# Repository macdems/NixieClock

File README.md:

# IN-14 Nixie Clock

A connected **IN-14 Nixie tube clock** combining classic display technology with modern embedded control.  
This repository contains the complete project: **firmware**, **electrical schematic**, **PCB design**, and **case design**.

## Overview

The project is built around an ESP-based controller and drives IN-14 Nixie tubes to display time with network-connected features such as:

- **Automatic time synchronization**
- **MQTT integration**
- **OTA firmware updates**
- **Persistent settings storage**

## Repository Contents

- **Firmware** — ESP-IDF project for clock control, MQTT, OTA, and LEDs
- **Schematic** — electrical design of the clock hardware
- **PCB** — board layout and manufacturing files
- **Case design** — enclosure files for the finished device

## Firmware Features

- IN-14 time display control
- Wi-Fi connectivity
- SNTP time synchronization
- MQTT status and command topics
- Home Assistant discovery support
- OTA firmware update over HTTPS
- LED effects and persisted LED state

## Hardware

This project is designed for **IN-14 Nixie tubes** and includes the supporting electronics required for:

- high-voltage tube driving
- logic/control circuitry
- power distribution
- decorative or ambient LED lighting

### Bill of Materials (BOM)

| Ref                                | Qty | Value               | Description                                                                       |
| ---------------------------------- | --- | ------------------- | --------------------------------------------------------------------------------- |
| C1                                 | 1   | 220µF/35V           | electrolytic capacitor THT radial D5.0mm P2.50mm                                  |
| C2                                 | 1   | 220µF               | electrolytic capacitor THT radial D5.0mm P2.50mm                                  |
| D1, D2, D3, D4                     | 4   | WS2812B             | WS2812B-1209 SMD mount LED                                                        |
| D5, D7                             | 2   | SS24                | SMA package                                                                       |
| D6                                 | 1   | ES1G                | SMA package                                                                       |
| HS1                                | 1   | T8WC                | heatsink for for TO-220 (<https://aliexpress.com/item/1005006082544471.html>)     |
| J1                                 | 1   | 12V                 | 01x02 screw terminal P5.08mm                                                      |
| J2                                 | 1   | 180V                | 01x02 screw terminal P5.08mm                                                      |
| L1                                 | 1   | 150mH               | SMD inductor L_10.4x10.4 H4.8                                                     |
| N1, N2, N3, N4                     | 4   | IN-14               | Nixie IN-14                                                                       |
| N5                                 | 1   |                     | 02×02 pin socket P2.54mm                                                          |
| N5                                 | 1   |                     | Nixie colon separator (<https://aliexpress.com/item/1005009385409998.html>)       |
| Q1, Q2, Q3, Q4, Q5, Q6, Q7, Q8, Q9 | 9   | MMBTA44             | SOT-23 package                                                                    |
| R1, R2, R3, R4                     | 4   | 12k                 | 1026 SMD                                                                          |
| R5, R6                             | 2   | 390k                | 1026 SMD                                                                          |
| U1, U2, U3, U4                     | 4   | SN74141N            | DIP-16 W7.62mm                                                                    |
| U5, U6, U7                         | 3   | 74HC595             | DIP-16 W7.62mm                                                                    |
| U8                                 | 1   | LM2596T-5           | TO-220-5                                                                          |
| U9                                 | 1   | ESP32-C3 Super Mini |                                                                                   |
|                                    | 1   | NCH6100HV           | high voltage DC power supply for Nixie tubes                                      |
|                                    | 6   | M3×5×4              | brass insert M3 H5mm OD4mm                                                        |
|                                    | 2   | M2.5×3×3.5          | brass insert M2.5 H3mm OD3.5mm                                                    |
|                                    | 1   | DC022B              | DC power jack supply socket (<https://aliexpress.com/item/1005005583190148.html>) |

### Manufacturing

1. Order the PCB from a manufacturer such as **JLCPCB** or **PCBWay**using the provided KICAD project files.
2. Assemble the components according to the schematic and PCB layout.
3. 3D print or fabricate the case using the provided FreeCAD design files.
4. Paint the case if desired and allow to dry before final assembly.
5. Mount the DC power jack and brass inserts into the case, then secure the PCB inside the case using screws and inserts.
6. Solder wires to the DC power jack and connect them to both 12V input of the PCB and the NCH6100HV power supply input. Ensure proper polarity and secure connections. 
7. Connect the NCH6100HV 180V output to the J2 high voltage input on the PCB, ensuring secure and insulated connections to prevent accidental contact with high voltage.

## Build

Firmware is based on **ESP-IDF**. First you need to configure it, specyfying your WiFi and MQTT creedentials. Then you can build and flash the firmware with:

```bash
idf.py build
idf.py -p <PORT> flash monitor
```

Configuration can be adjusted with:

```bash
idf.py menuconfig
```

## Project Structure

```text
main/               ESP-IDF application sources
PCB/                PCB layout and fabrication files
NixieClock.FCStd    FreeCAD case design file
NixieClock.3mf      Case design export for 3D printing
```

## Notes

Nixie clocks operate with **high voltage**. Hardware assembly, probing, and testing should be performed carefully and only with appropriate experience.

## License

This project is licensed under the **Creative Commons Attribution-ShareAlike 4.0 International (CC BY-SA 4.0)** license.  
See the [`LICENSE.md`](LICENSE.md) file for full license text.

## Status

This repository is intended as a complete source package for building an IN-14 Nixie clock from electronics to enclosure.

---
A compact Nixie clock project with both vintage character and modern connectivity.

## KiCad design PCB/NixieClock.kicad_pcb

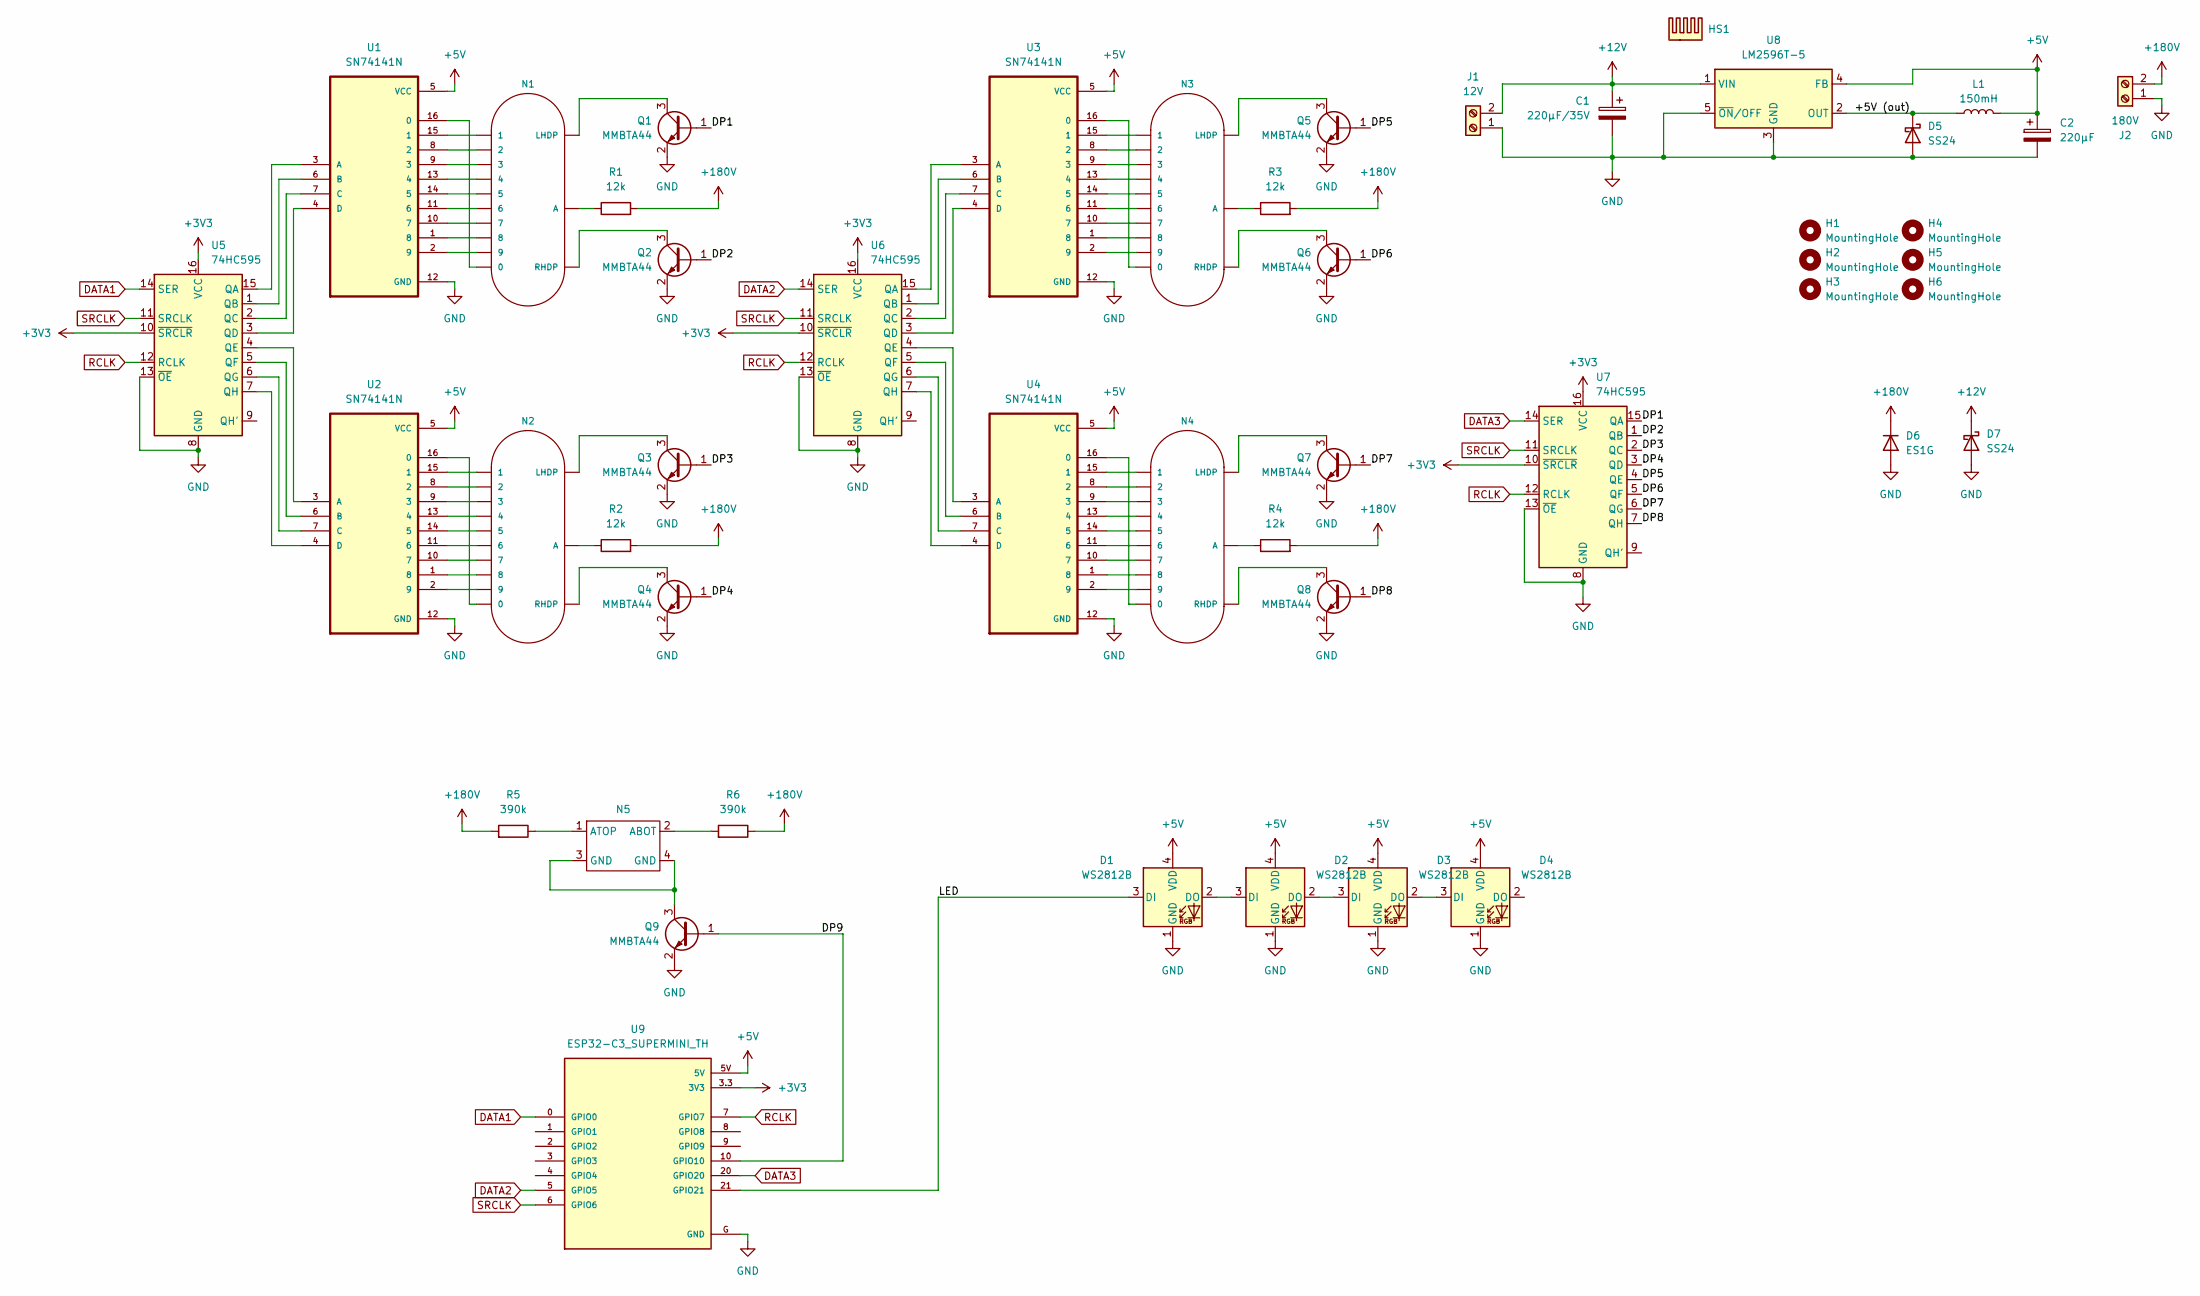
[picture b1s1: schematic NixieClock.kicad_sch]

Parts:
C1: 220µF/35V; CP_Radial_D5.0mm_P2.50mm
C2: 220µF; CP_Radial_D5.0mm_P2.50mm
D1, D2, D3, D4: WS2812B; LED-SMD_4P-L3.2-W2.7-TL-WS2812B-1209
D5, D7: SS24; D_SMA_Handsoldering
D6: ES1G; D_SMA_Handsoldering
H1, H2, H3, H4, H5, H6: MountingHole; MountingHole_3.2mm_M3
HS1: Heatsink; Heatsink_T8WC_TO-220
J1: 12V; TerminalBlock_bornier-2_P5.08mm
J2: 180V; TerminalBlock_bornier-2_P5.08mm
L1: 150mH; L_10.4x10.4_H4.8
N1, N2, N3, N4: IN-14
N5: PinSocket_2x02_P2.54mm_Vertical
Q1, Q2, Q3, Q4, Q5, Q6, Q7, Q8, Q9: MMBTA44; SOT-23_Handsoldering
R1, R2, R3, R4: 12k; R_1206_3216Metric_Pad1.30x1.75mm_HandSolder
R5, R6: 390k; R_1206_3216Metric_Pad1.30x1.75mm_HandSolder
U1, U2, U3, U4: SN74141N; DIP-16_W7.62mm
U5, U6, U7: 74HC595; DIP-16_W7.62mm
U8: LM2596T-5; TO-220-5_P3.4x3.7mm_StaggerOdd_Lead3.8mm_Vertical
U9: ESP32-C3_SUPERMINI_TH; MODULE_ESP32-C3_SUPERMINI_TH

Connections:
+3V3: U5.10 (~SRCLR), U5.16 (VCC), U6.10 (~SRCLR), U6.16 (VCC), U7.10 (~SRCLR), U7.16 (VCC), U9.3.3 (3V3)
+5V: C2.1, D1.4 (VDD), D2.4 (VDD), D3.4 (VDD), D4.4 (VDD), L1.2, U1.5 (VCC), U2.5 (VCC), U3.5 (VCC), U4.5 (VCC), U8.4 (FB), U9.5V
+12V: C1.1, D7.1 (K), J1.2, U8.1 (VIN)
+180V: D6.1 (K), J2.2, R1.2, R2.2, R3.2, R4.2, R5.2, R6.1
/+5V (out): D5.1 (K), L1.1, U8.2 (OUT)
/DP1: Q1.1 (B), U7.15 (QA)
/DP2: Q2.1 (B), U7.1 (QB)
/DP3: Q3.1 (B), U7.2 (QC)
/DP4: Q4.1 (B), U7.3 (QD)
/DP5: Q5.1 (B), U7.4 (QE)
/DP6: Q6.1 (B), U7.5 (QF)
/DP7: Q7.1 (B), U7.6 (QG)
/DP8: Q8.1 (B), U7.7 (QH)
/DP9: Q9.1 (B), U9.10 (GPIO10)
/LED: D1.3 (DI), U9.21 (GPIO21)
DATA1: U5.14 (SER), U9.0 (GPIO0)
DATA2: U6.14 (SER), U9.5 (GPIO5)
DATA3: U7.14 (SER), U9.20 (GPIO20)
GND: C1.2, C2.2, D1.1 (GND), D2.1 (GND), D3.1 (GND), D4.1 (GND), D5.2 (A), D6.2 (A), D7.2 (A), J1.1, J2.1, Q1.2 (E), Q2.2 (E), Q3.2 (E), Q4.2 (E), Q5.2 (E), Q6.2 (E), Q7.2 (E), Q8.2 (E), Q9.2 (E), U1.12 (GND), U2.12 (GND), U3.12 (GND), U4.12 (GND), U5.8 (GND), U5.13 (~OE), U6.8 (GND), U6.13 (~OE), U7.8 (GND), U7.13 (~OE), U8.3 (GND), U8.5 (~ON/OFF), U9.G (GND)
unnamed: D1.2 (DO), D2.3 (DI)
unnamed: D2.2 (DO), D3.3 (DI)
unnamed: D3.2 (DO), D4.3 (DI)
unnamed: N1.A, R1.1
unnamed: N2.A, R2.1
unnamed: N3.A, R3.1
unnamed: N4.A, R4.1
unnamed: N5.2 (ABOT), R6.2
unnamed: N5.1 (ATOP), R5.1
unnamed: N1.LHDP, Q1.3 (C)
unnamed: N1.RHDP, Q2.3 (C)
unnamed: N2.LHDP, Q3.3 (C)
unnamed: N2.RHDP, Q4.3 (C)
unnamed: N3.LHDP, Q5.3 (C)
unnamed: N3.RHDP, Q6.3 (C)
unnamed: N4.LHDP, Q7.3 (C)
unnamed: N4.RHDP, Q8.3 (C)
unnamed: N5.3 (GND), N5.4 (GND), Q9.3 (C)
unnamed: N1.0, U1.16 (0)
unnamed: N1.1, U1.15 (1)
unnamed: N1.2, U1.8 (2)
unnamed: N1.3, U1.9 (3)
unnamed: N1.4, U1.13 (4)
unnamed: N1.5, U1.14 (5)
unnamed: N1.6, U1.11 (6)
unnamed: N1.7, U1.10 (7)
unnamed: N1.8, U1.1 (8)
unnamed: N1.9, U1.2 (9)
unnamed: U1.3 (A), U5.15 (QA)
unnamed: U1.6 (B), U5.1 (QB)
unnamed: U1.7 (C), U5.2 (QC)
unnamed: U1.4 (D), U5.3 (QD)
unnamed: N2.0, U2.16 (0)
unnamed: N2.1, U2.15 (1)
unnamed: N2.2, U2.8 (2)
unnamed: N2.3, U2.9 (3)
unnamed: N2.4, U2.13 (4)
unnamed: N2.5, U2.14 (5)
unnamed: N2.6, U2.11 (6)
unnamed: N2.7, U2.10 (7)
unnamed: N2.8, U2.1 (8)
unnamed: N2.9, U2.2 (9)
unnamed: U2.3 (A), U5.4 (QE)
unnamed: U2.6 (B), U5.5 (QF)
unnamed: U2.7 (C), U5.6 (QG)
unnamed: U2.4 (D), U5.7 (QH)
unnamed: N3.0, U3.16 (0)
unnamed: N3.1, U3.15 (1)
unnamed: N3.2, U3.8 (2)
unnamed: N3.3, U3.9 (3)
unnamed: N3.4, U3.13 (4)
unnamed: N3.5, U3.14 (5)
unnamed: N3.6, U3.11 (6)
unnamed: N3.7, U3.10 (7)
unnamed: N3.8, U3.1 (8)
unnamed: N3.9, U3.2 (9)
unnamed: U3.3 (A), U6.15 (QA)
unnamed: U3.6 (B), U6.1 (QB)
unnamed: U3.7 (C), U6.2 (QC)
unnamed: U3.4 (D), U6.3 (QD)
unnamed: N4.0, U4.16 (0)
unnamed: N4.1, U4.15 (1)
unnamed: N4.2, U4.8 (2)
unnamed: N4.3, U4.9 (3)
unnamed: N4.4, U4.13 (4)
unnamed: N4.5, U4.14 (5)
unnamed: N4.6, U4.11 (6)
unnamed: N4.7, U4.10 (7)
unnamed: N4.8, U4.1 (8)
unnamed: N4.9, U4.2 (9)
unnamed: U4.3 (A), U6.4 (QE)
unnamed: U4.6 (B), U6.5 (QF)
unnamed: U4.7 (C), U6.6 (QG)
unnamed: U4.4 (D), U6.7 (QH)
RCLK: U5.12 (RCLK), U6.12 (RCLK), U7.12 (RCLK), U9.7 (GPIO7)
SRCLK: U5.11 (SRCLK), U6.11 (SRCLK), U7.11 (SRCLK), U9.6 (GPIO6)

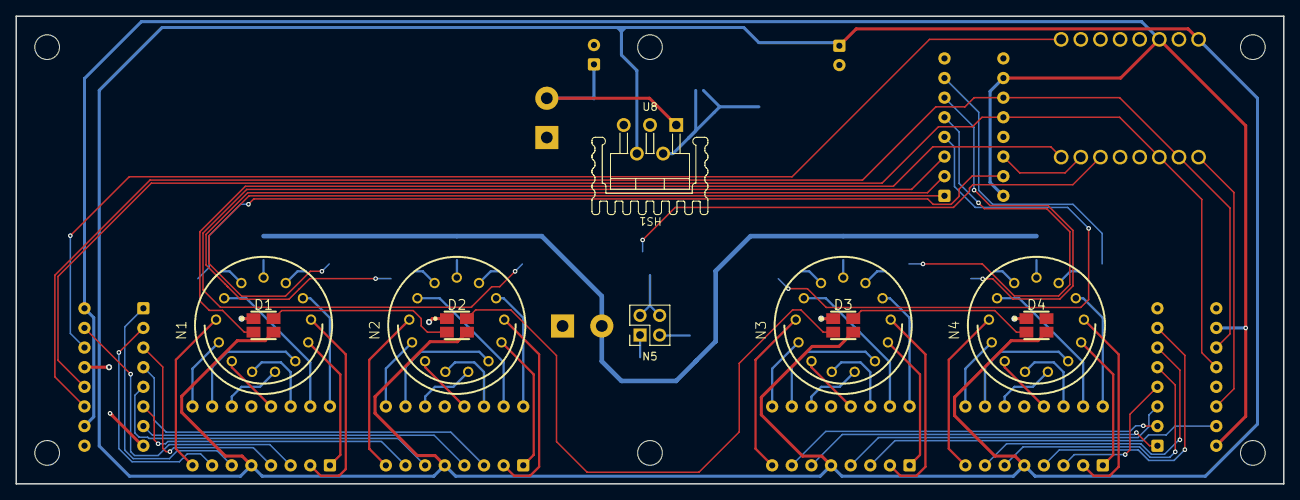
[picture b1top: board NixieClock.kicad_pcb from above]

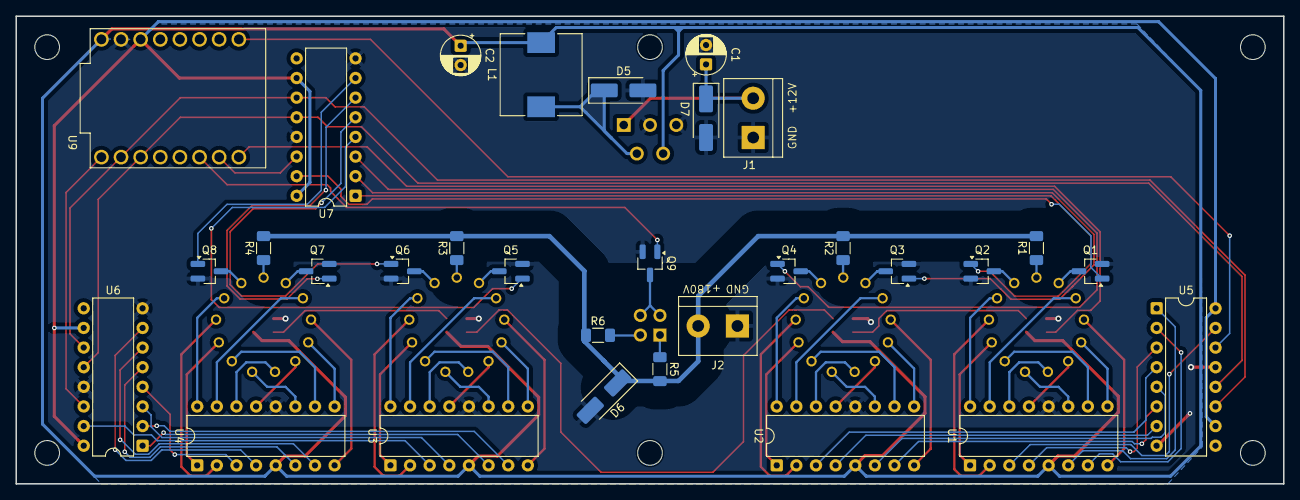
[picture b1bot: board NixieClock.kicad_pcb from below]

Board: 2 copper layers, 164.0 x 60.5 mm, 48 parts (31 on the bottom side), 95 nets.

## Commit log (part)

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2026-04-13 Initial appication framework
2026-04-13 Update letsencrypt certificate
2026-04-13 Make publishable project
2026-04-13 Some minor MQTT improvements
2026-04-13 Improvements in Python scripts
2026-04-16 Add BOM and manufacturing instructions to README
2026-04-28 Fix MQTT discovery and RSSI timer
2026-06-08 Remove private data from settings
